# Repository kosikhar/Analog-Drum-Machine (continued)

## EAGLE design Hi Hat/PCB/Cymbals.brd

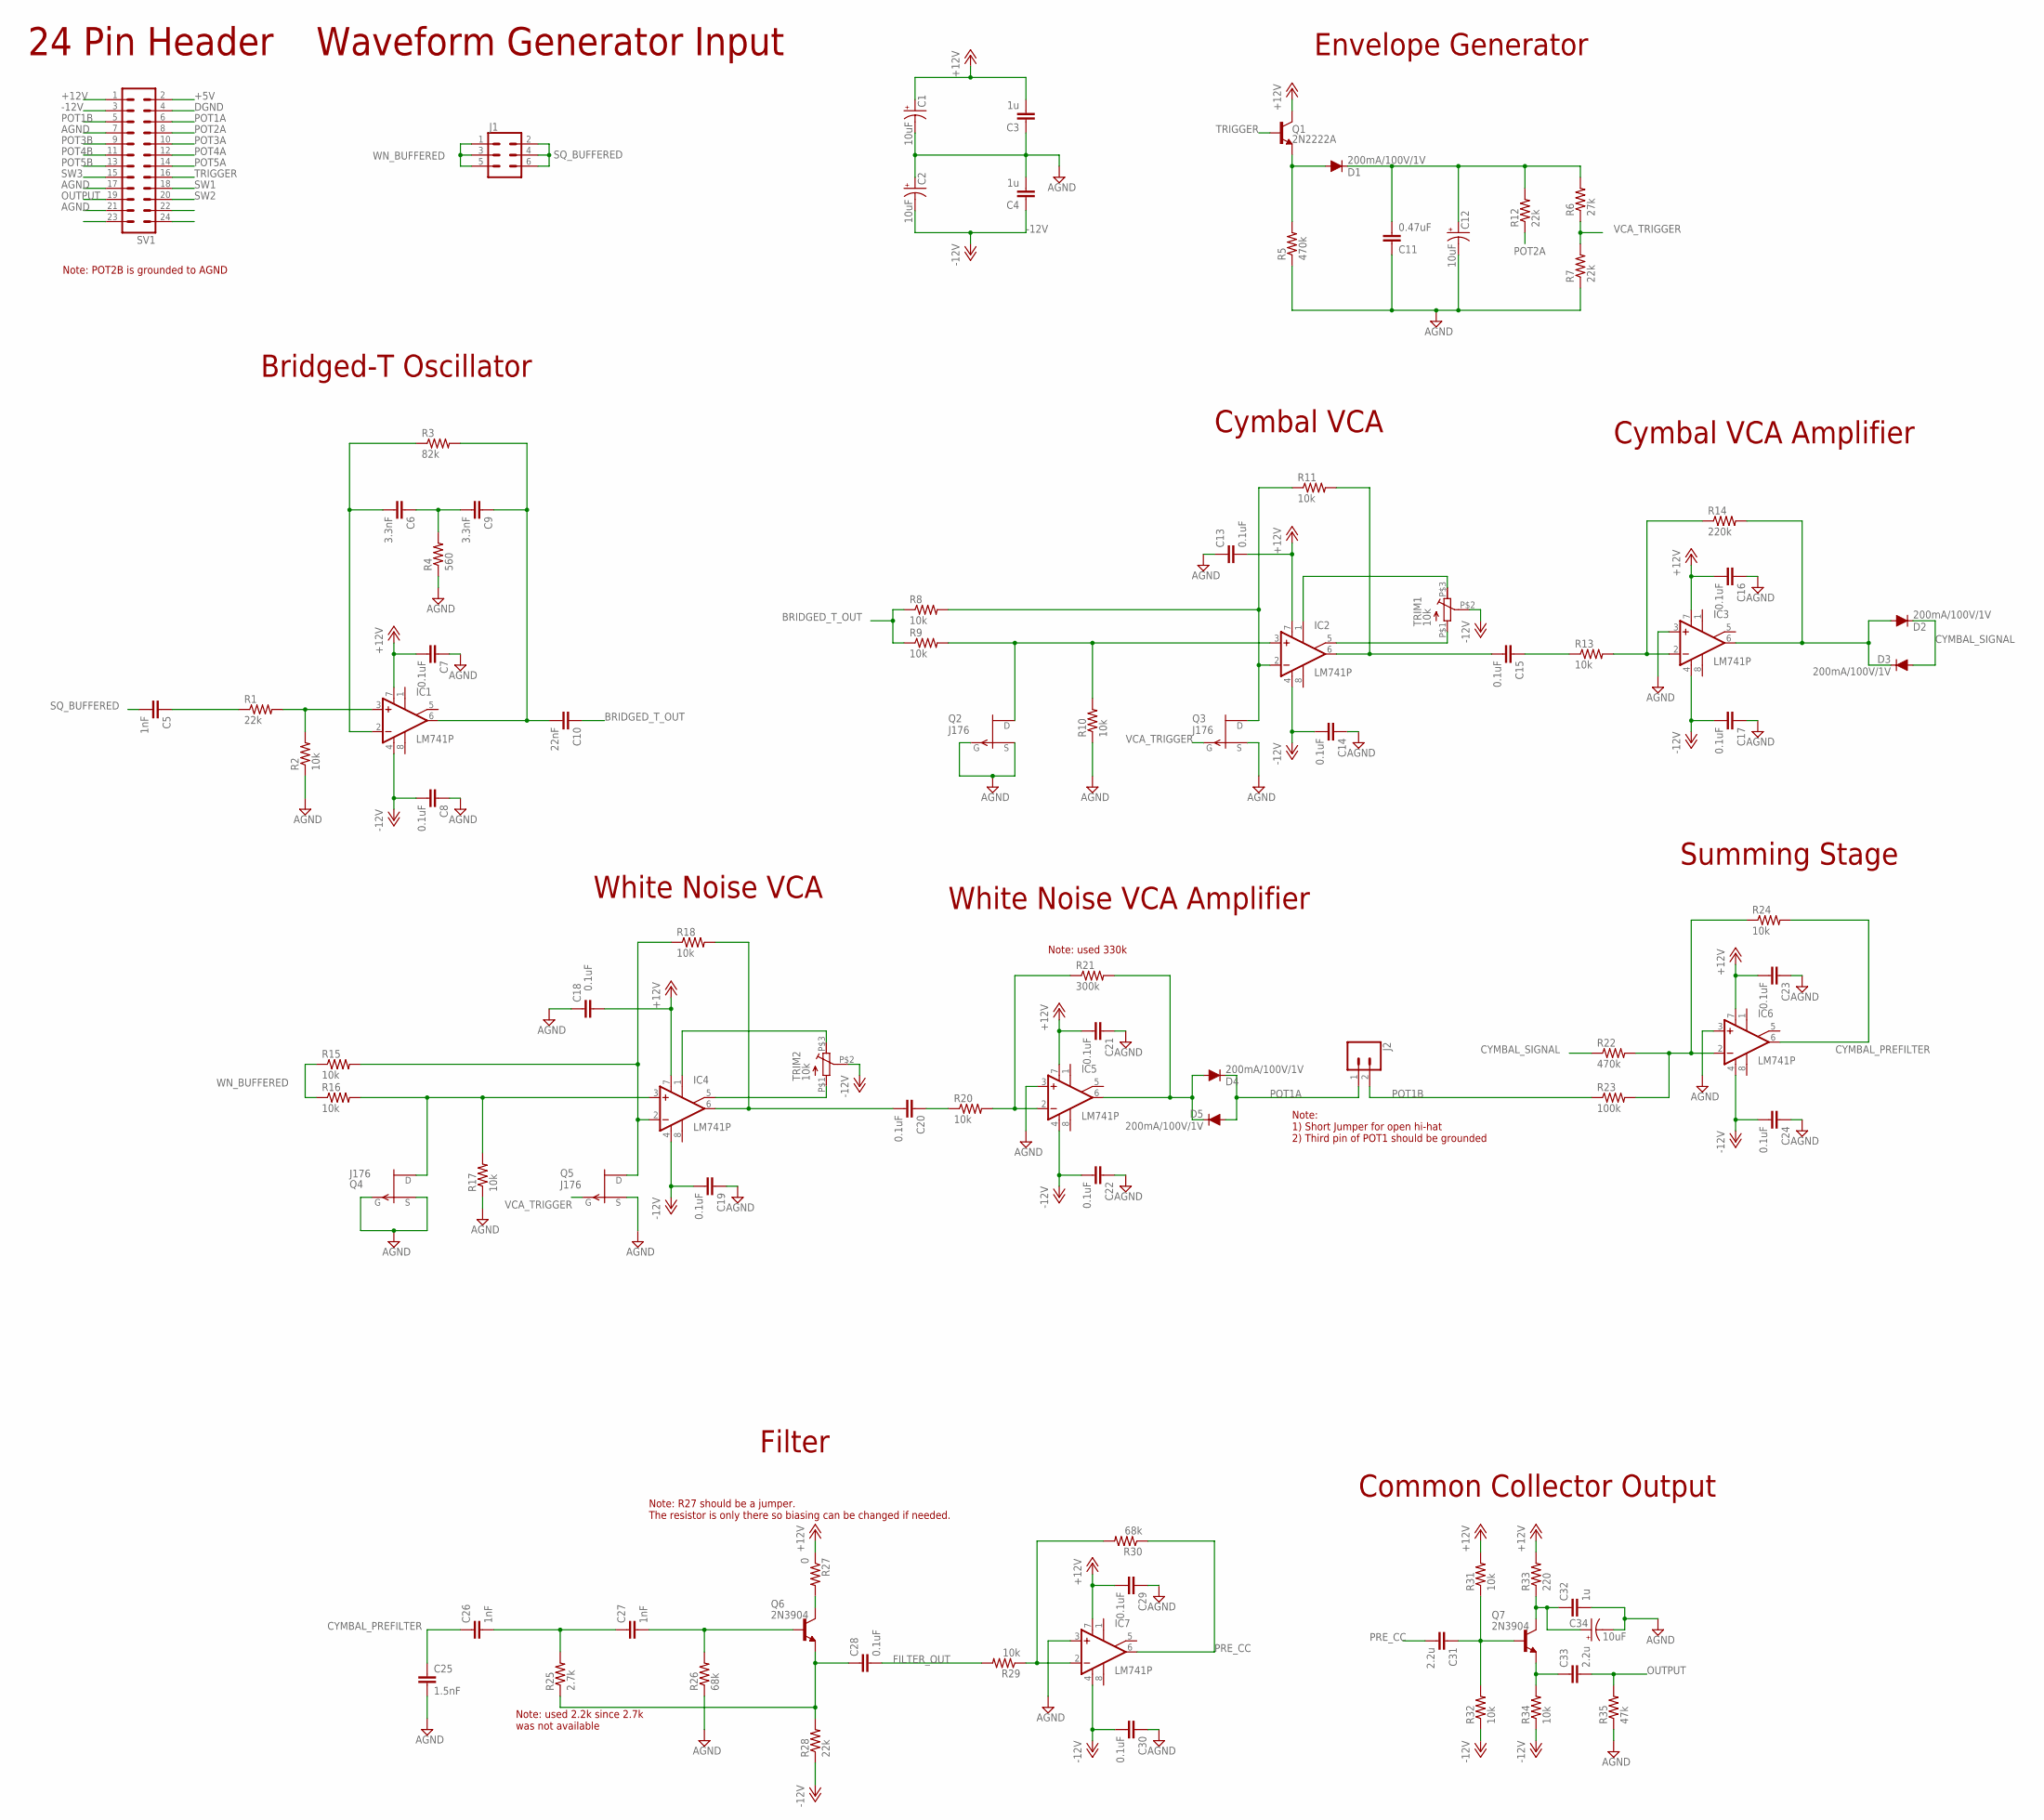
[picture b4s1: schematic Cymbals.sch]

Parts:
C1, C2, C12, C34: 10uF; E2,5-6
C3, C4, C32: 1u; C050-024X044
C5, C26, C27: 1nF; C050-024X044
C6, C9: 3.3nF; C050-024X044
C7, C8, C13, C14, C15, C16, C17, C18, C19, C20, C21, C22, C23, C24, C28, C29, C30: 0.1uF; C050-024X044
C10: 22nF; C050-024X044
C11: 0.47uF; C050-024X044
C25: 1.5nF; C050-024X044
C31, C33: 2.2u; C050-024X044
D1, D2, D3, D4, D5: 200mA/100V/1V; DIODE-1N4148
IC1, IC2, IC3, IC4, IC5, IC6, IC7: LM741P; DIL08
J1: CONN_03X2NO_SILK; 2X3-NS
J2: CONN_02; 1X02
Q1: 2N2222A; TO-92
Q2, Q3, Q4, Q5: J176; TO-92
Q6, Q7: 2N3904; TO92
R1, R7, R12, R28: 22k; 0207/7
R2, R8, R9, R10, R11, R13, R15, R16, R17, R18, R20, R24, R29, R31, R32, R34: 10k; 0207/7
R3: 82k; 0207/7
R4: 560; 0207/7
R5, R22: 470k; 0207/7
R6: 27k; 0207/7
R14: 220k; 0207/7
R21: 300k; 0207/7
R23: 100k; 0207/7
R25: 2.7k; 0207/7
R26, R30: 68k; 0207/7
R27: 0; 0207/7
R33: 220; 0207/7
R35: 47k; 0207/7
SV1: MA12-2
TRIM1, TRIM2: 10k; 10K_TRIM

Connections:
+5V: SV1.2
+12V: C1.+, C3.2, C7.2, C13.2, C16.2, C18.2, C21.2, C23.2, C29.2, IC1.7 (V+), IC2.7 (V+), IC3.7 (V+), IC4.7 (V+), IC5.7 (V+), IC6.7 (V+), IC7.7 (V+), Q1.1 (C), R27.1, R31.2, R33.2, SV1.1
-12V: C2.-, C4.1, C8.2, C14.2, C17.2, C19.2, C22.2, C24.2, C30.2, IC1.4 (V-), IC2.4 (V-), IC3.4 (V-), IC4.4 (V-), IC5.4 (V-), IC6.4 (V-), IC7.4 (V-), R28.1, R32.1, R34.1, SV1.3, TRIM1.P$2 (S), TRIM2.P$2 (S)
AGND: C1.-, C2.+, C3.1, C4.2, C7.1, C8.1, C11.1, C12.-, C13.1, C14.1, C16.1, C17.1, C18.1, C19.1, C21.1, C22.1, C23.1, C24.1, C25.2, C29.1, C30.1, C32.2, C34.-, IC3.3 (+IN), IC5.3 (+IN), IC6.3 (+IN), IC7.3 (+IN), Q2.2 (G), Q2.3 (S), Q3.3 (S), Q4.2 (G), Q4.3 (S), Q5.3 (S), R2.1, R4.1, R5.1, R7.1, R10.1, R17.1, R26.1, R35.1, SV1.7, SV1.17, SV1.21
BRIDGED_T_OUT: C10.1, R8.1, R9.1
CYMBAL_PREFILTER: C25.1, C26.1, IC6.6 (OUT), R24.2
CYMBAL_SIGNAL: D2.C, D3.A, R22.1
DGND: SV1.4
FILTER_OUT: C28.2, R29.2
unnamed: C15.2, IC2.6 (OUT), R11.2
unnamed: IC2.3 (+IN), Q2.1 (D), R9.2, R10.2
unnamed: IC2.2 (-IN), Q3.1 (D), R8.2, R11.1
unnamed: IC2.5 (ON2), TRIM1.P$1 (A)
unnamed: Q6.1 (C), R27.2
unnamed: C11.2, C12.+, D1.C, R6.2, R12.2
unnamed: IC2.1 (ON1), TRIM1.P$3 (E)
unnamed: IC3.2 (-IN), R13.2, R14.1
unnamed: IC6.2 (-IN), R22.2, R23.2, R24.1
unnamed: C6.2, IC1.2 (-IN), R3.1
unnamed: C15.1, R13.1
unnamed: IC5.2 (-IN), R20.2, R21.1
unnamed: IC7.2 (-IN), R29.1, R30.2
unnamed: C20.1, R20.1
unnamed: C20.2, IC4.6 (OUT), R18.2
unnamed: D4.A, D5.C, IC5.6 (OUT), R21.2
unnamed: D2.A, D3.C, IC3.6 (OUT), R14.2
unnamed: C6.1, C9.2, R4.2
unnamed: C9.1, C10.2, IC1.6 (OUT), R3.2
unnamed: IC1.3 (+IN), R1.2, R2.2
unnamed: C5.1, R1.1
unnamed: C31.1, Q7.2 (B), R31.1, R32.2
unnamed: D1.A, Q1.3 (E), R5.2
unnamed: IC4.3 (+IN), Q4.1 (D), R16.2, R17.2
unnamed: IC4.2 (-IN), Q5.1 (D), R15.2, R18.1
unnamed: IC4.5 (ON2), TRIM2.P$1 (A)
unnamed: IC4.1 (ON1), TRIM2.P$3 (E)
unnamed: C33.1, Q7.3 (E), R34.2
unnamed: C32.1, C34.+, Q7.1 (C), R33.1
unnamed: C26.2, C27.1, R25.2
unnamed: C27.2, Q6.2 (B), R26.2
unnamed: C28.1, Q6.3 (E), R25.1, R28.2
OUTPUT: C33.2, R35.2, SV1.19
POT1A: D4.C, D5.A, J2.1, SV1.6
POT1B: J2.2, R23.1, SV1.5
POT2A: R12.1, SV1.8
POT3A: SV1.10
POT3B: SV1.9
POT4A: SV1.12
POT4B: SV1.11
POT5A: SV1.14
POT5B: SV1.13
PRE_CC: C31.2, IC7.6 (OUT), R30.1
SQ_BUFFERED: C5.2, J1.2, J1.4, J1.6
SW1: SV1.18
SW2: SV1.20
SW3: SV1.15
TRIGGER: Q1.2 (B), SV1.16
VCA_TRIGGER: Q3.2 (G), Q5.2 (G), R6.1, R7.2
WN_BUFFERED: J1.1, J1.3, J1.5, R15.1, R16.1

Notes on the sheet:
Note: 1) Short Jumper for open hi-hat 2) Third pin of POT1 should be grounded
Note: POT2B is grounded to AGND
Note: R27 should be a jumper. The resistor is only there so biasing can be changed if needed.
Note: used 330k
Note: used 2.2k since 2.7k was not available
24 Pin Header
Waveform Generator Input
Bridged-T Oscillator
Envelope Generator
Cymbal VCA
Cymbal VCA Amplifier
White Noise VCA
White Noise VCA Amplifier
Summing Stage
Filter
Common Collector Output

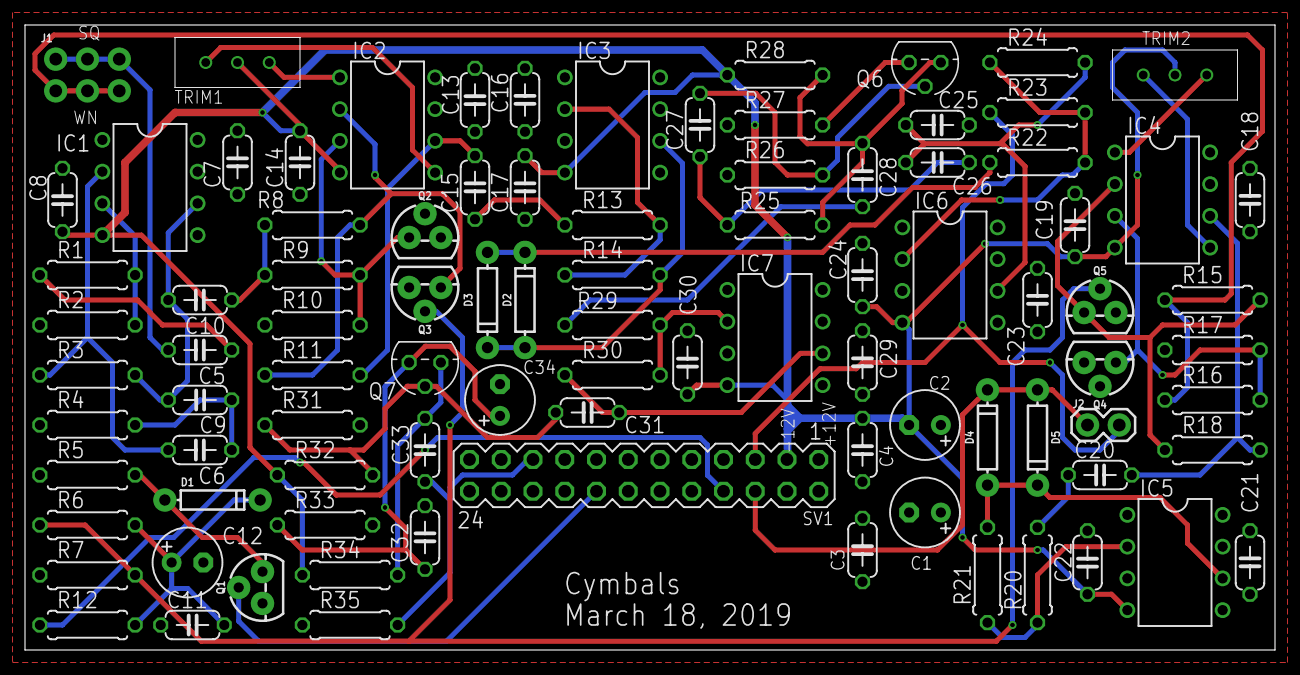
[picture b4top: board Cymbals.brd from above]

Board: 2 copper layers, 100.0 x 50.0 mm, 92 parts (0 on the bottom side), 48 nets.

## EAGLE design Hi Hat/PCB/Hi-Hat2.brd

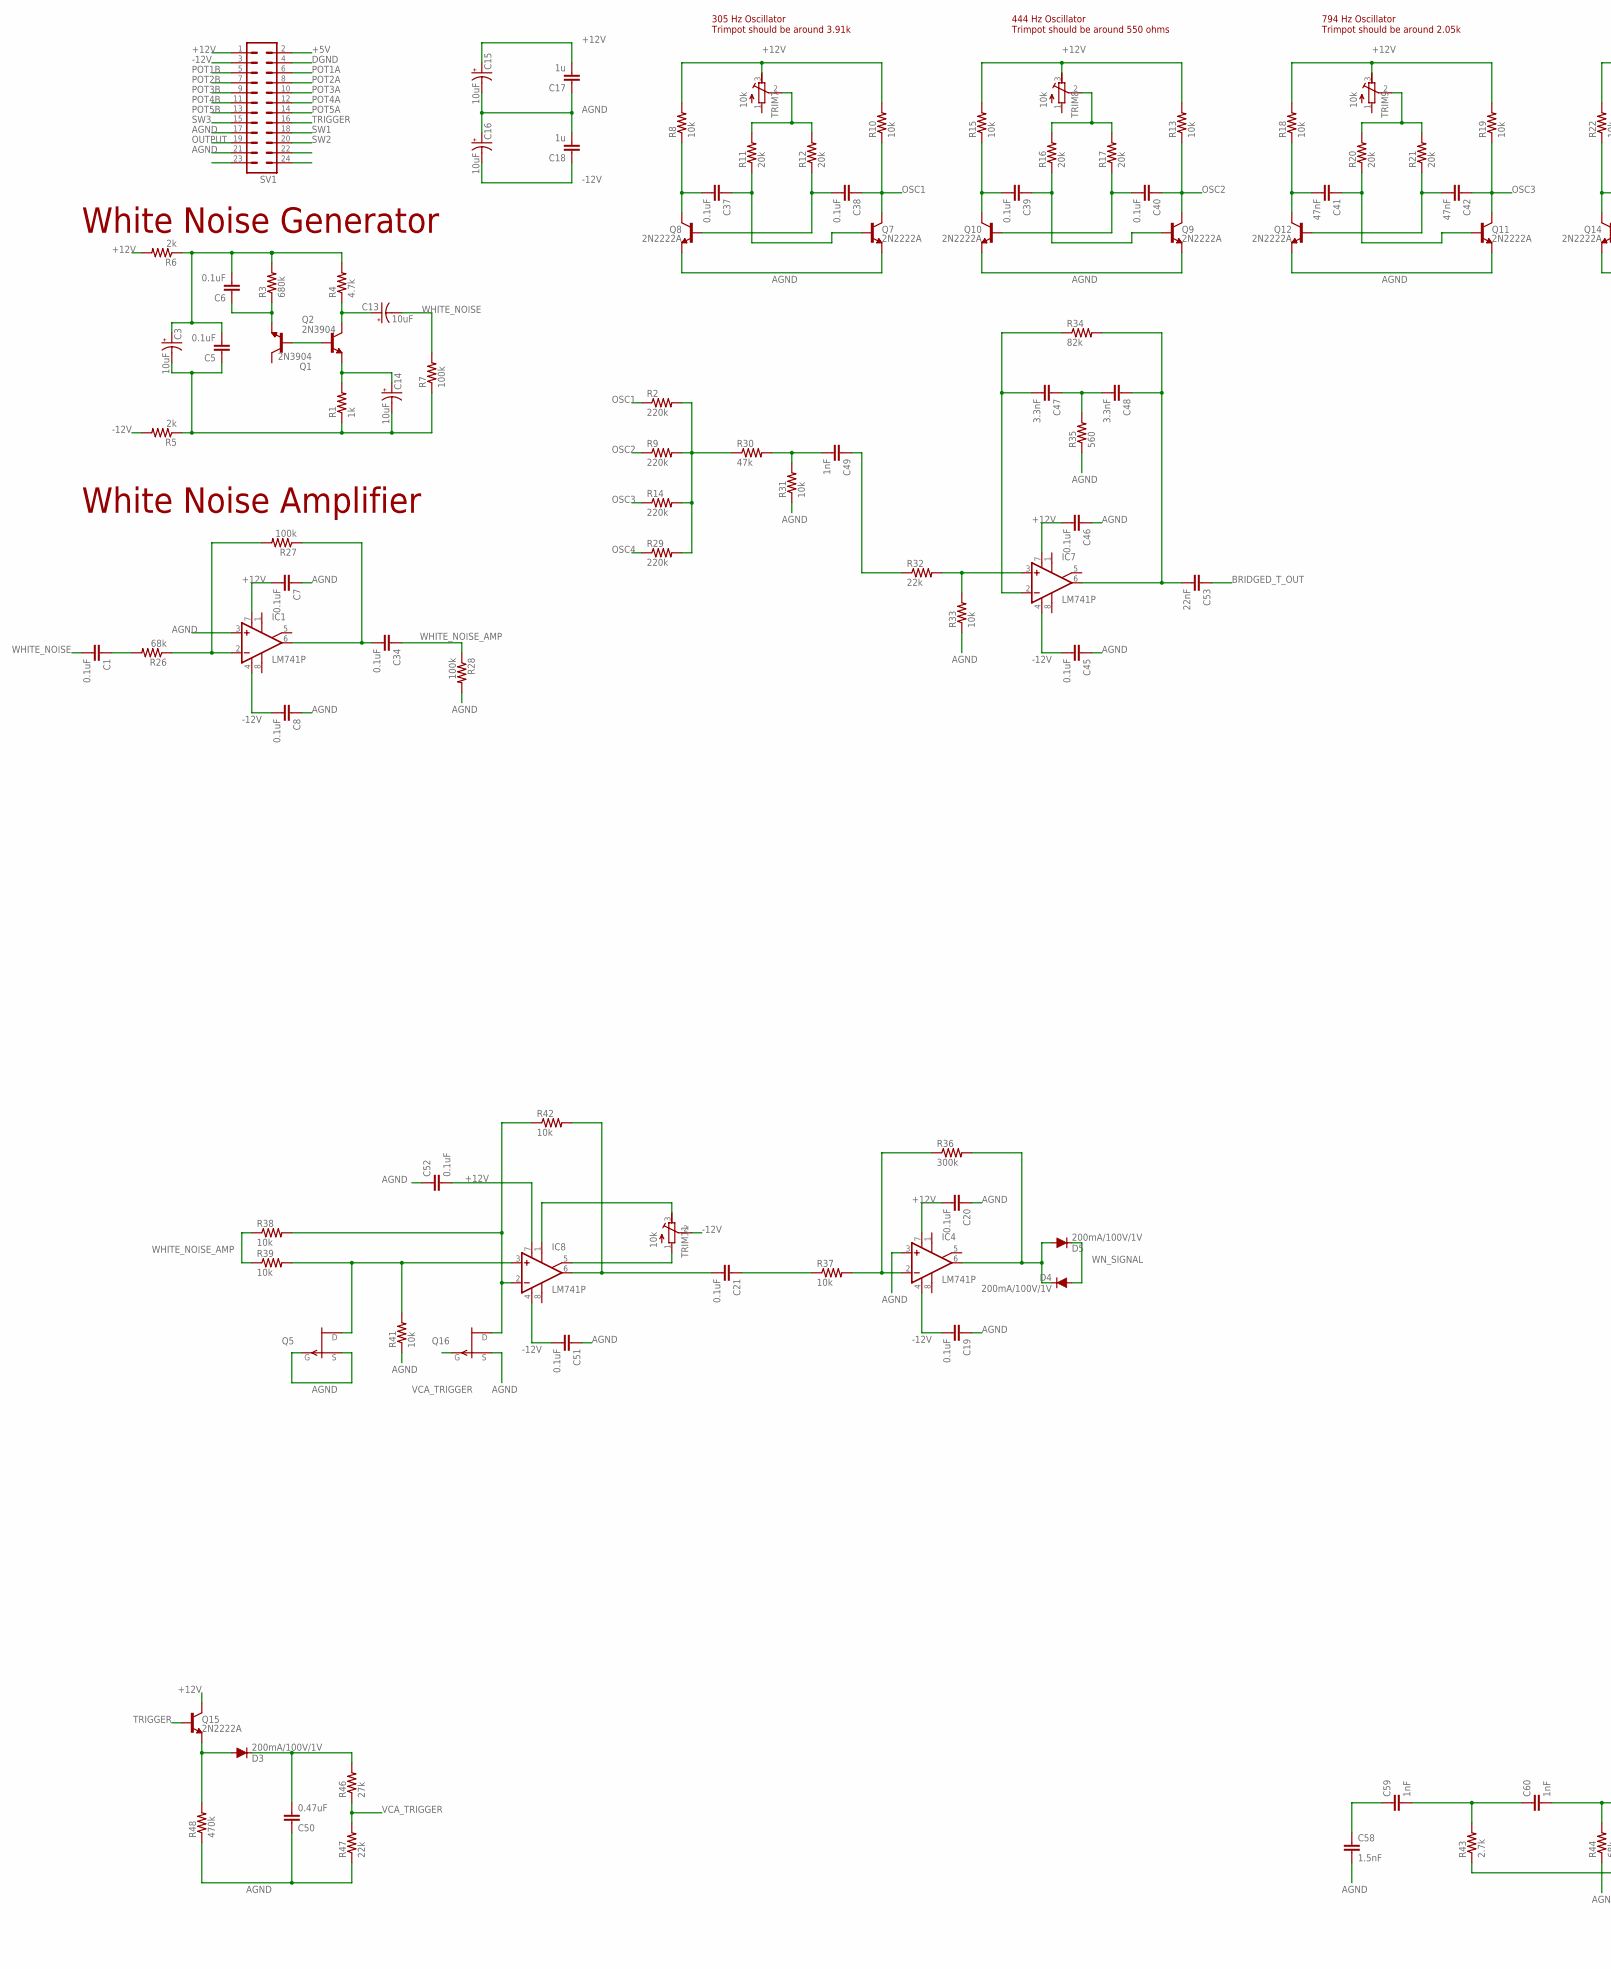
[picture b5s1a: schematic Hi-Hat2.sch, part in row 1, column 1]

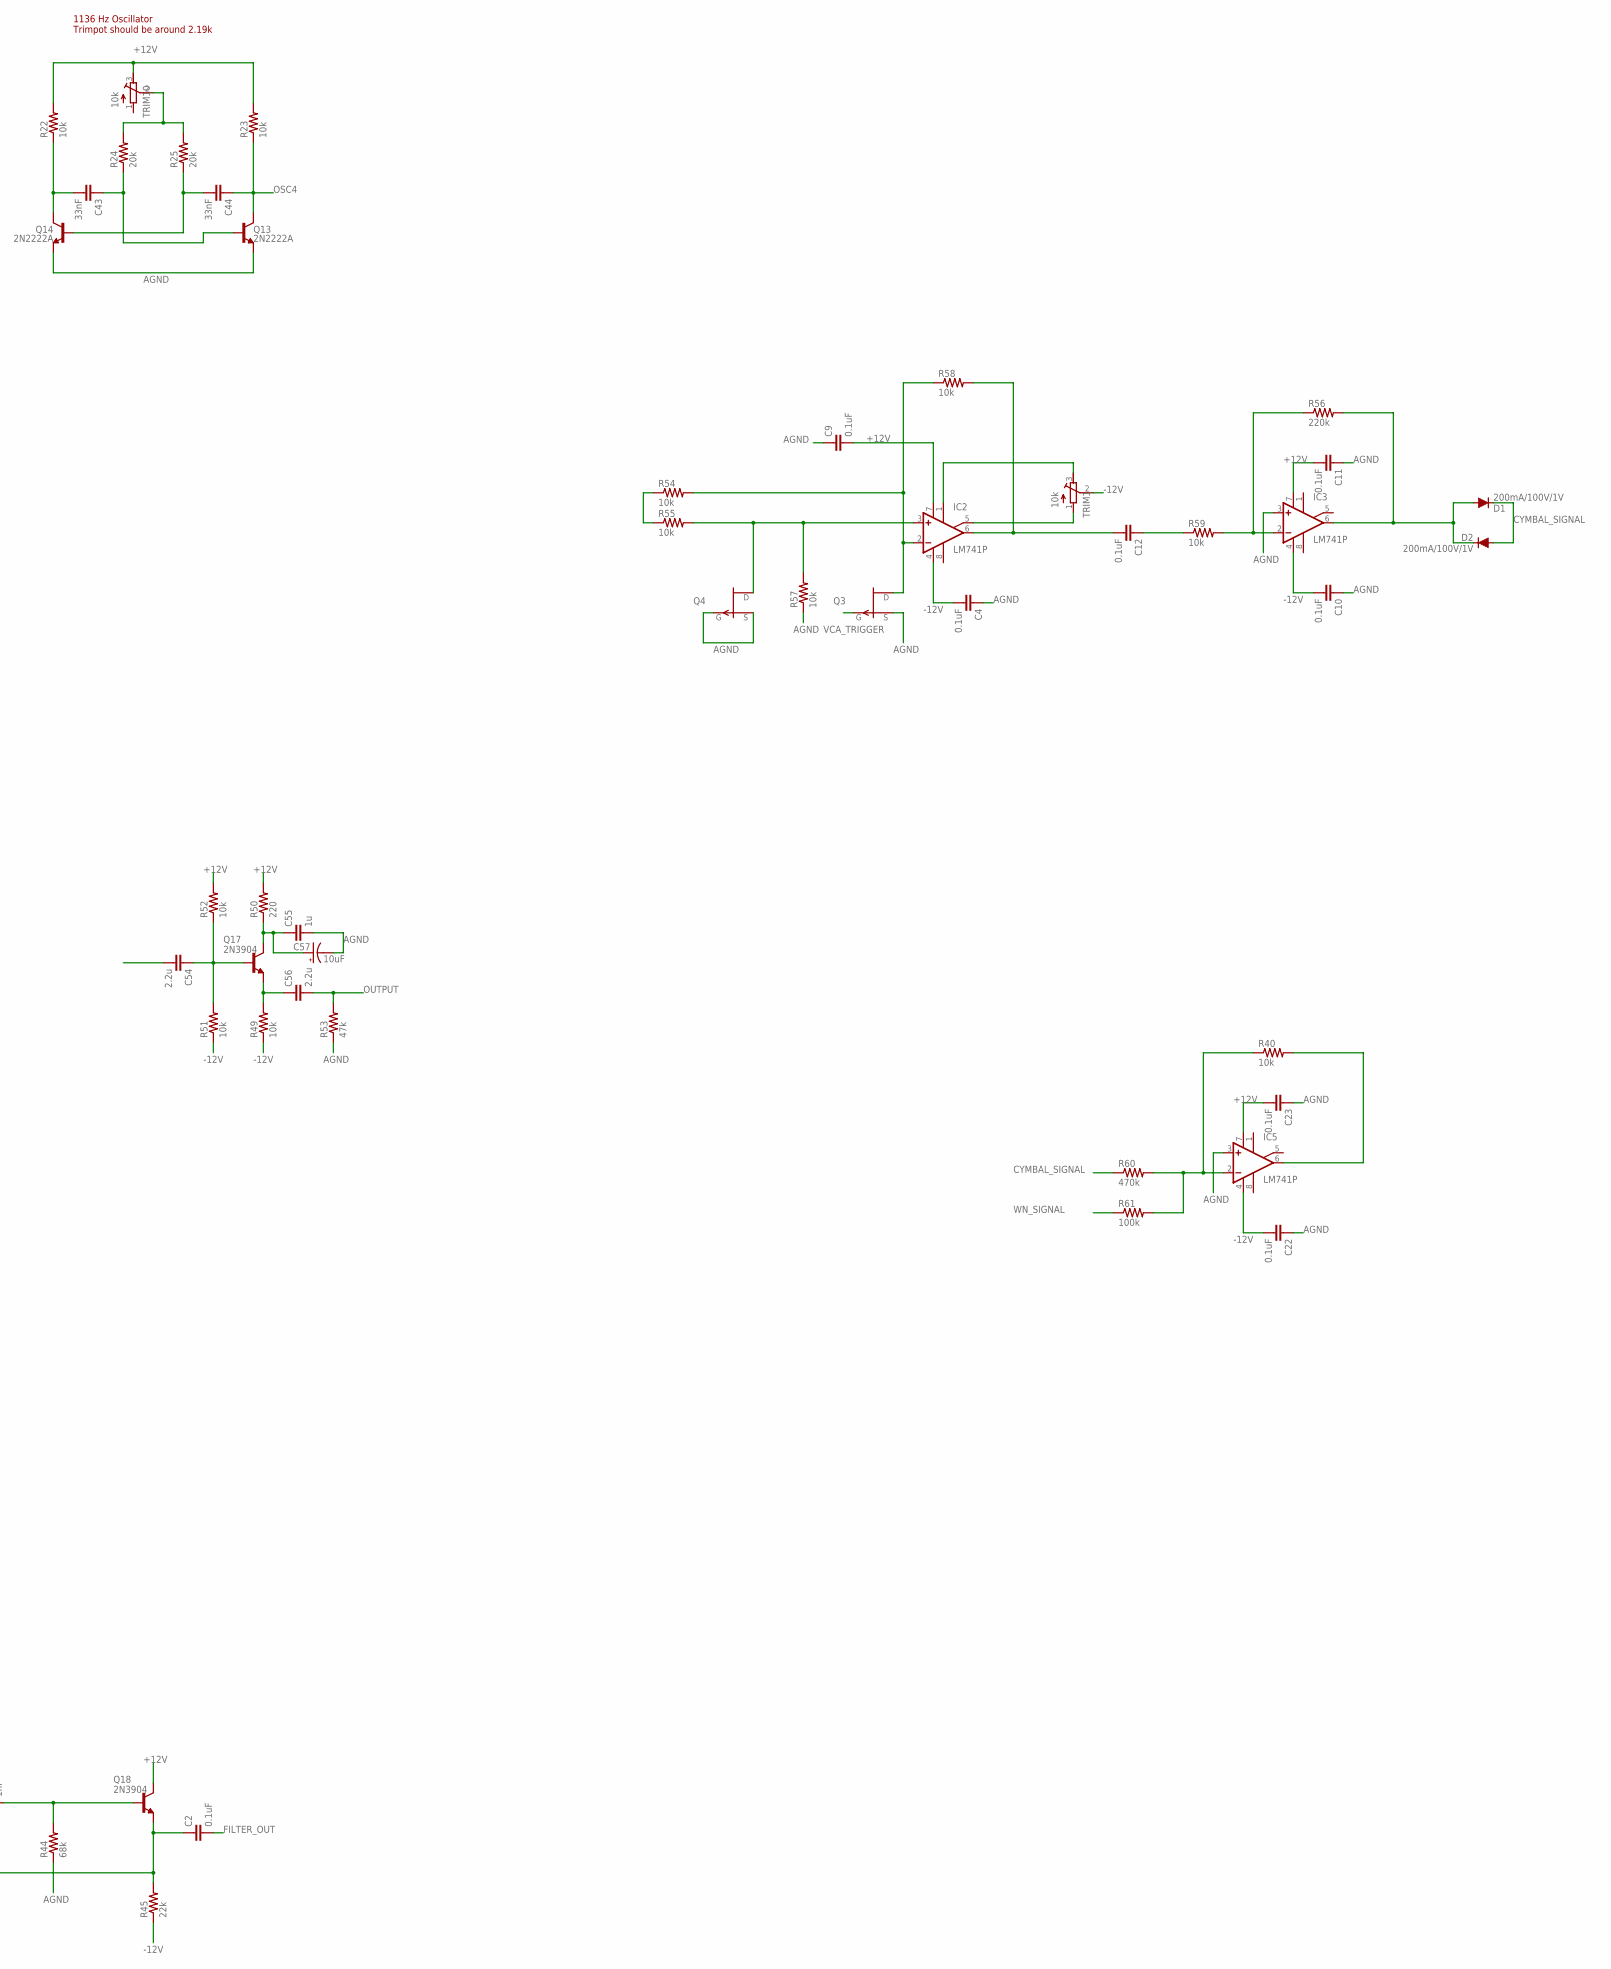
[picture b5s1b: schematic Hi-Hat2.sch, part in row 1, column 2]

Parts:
C1, C2, C4, C5, C6, C7, C8, C9, C10, C11, C12, C19, C20, C21, C22, C23, C34, C37, C38, C39, C40, C45, C46, C51, C52: 0.1uF; C050-024X044
C3, C13, C14, C15, C16, C57: 10uF; E2,5-6
C17, C18, C55: 1u; C050-024X044
C41, C42: 47nF; C050-024X044
C43, C44: 33nF; C050-024X044
C47, C48: 3.3nF; C050-024X044
C49, C59, C60: 1nF; C050-024X044
C50: 0.47uF; C050-024X044
C53: 22nF; C050-024X044
C54, C56: 2.2u; C050-024X044
C58: 1.5nF; C050-024X044
D1, D2, D3, D4, D5: 200mA/100V/1V; DIODE-1N4148
IC1, IC2, IC3, IC4, IC5, IC7, IC8: LM741P; DIL08
Q1, Q2, Q17, Q18: 2N3904; TO92
Q3, Q4, Q5, Q16: J176; TO-92
Q7, Q8, Q9, Q10, Q11, Q12, Q13, Q14, Q15: 2N2222A; TO-92
R1: 1k; 0207/7
R2, R9, R14, R29, R56: 220k; 0207/7
R3: 680k; 0207/7
R4: 4.7k; 0207/7
R5, R6: 2k; 0207/7
R7, R27, R28, R61: 100k; 0207/7
R8, R10, R13, R15, R18, R19, R22, R23, R31, R33, R37, R38, R39, R40, R41, R42, R49, R51, R52, R54, R55, R57, R58, R59: 10k; 0207/7
R11, R12, R16, R17, R20, R21, R24, R25: 20k; 0207/7
R26, R44: 68k; 0207/7
R30, R53: 47k; 0207/7
R32, R45, R47: 22k; 0207/7
R34: 82k; 0207/7
R35: 560; 0207/7
R36: 300k; 0207/7
R43: 2.7k; 0207/7
R46: 27k; 0207/7
R48, R60: 470k; 0207/7
R50: 220; 0207/7
SV1: MA12-2
TRIM1, TRIM7, TRIM8, TRIM9, TRIM10, TRIM11: 10k; RTRIM64W

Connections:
+5V: SV1.2
+12V: C7.2, C9.2, C11.2, C15.+, C17.2, C20.2, C23.2, C46.2, C52.2, IC1.7 (V+), IC2.7 (V+), IC3.7 (V+), IC4.7 (V+), IC5.7 (V+), IC7.7 (V+), IC8.7 (V+), Q15.1 (C), Q18.1 (C), R6.2, R8.2, R10.2, R13.2, R15.2, R18.2, R19.2, R22.2, R23.2, R50.2, R52.2, SV1.1, TRIM7.3 (E), TRIM8.3 (E), TRIM9.3 (E), TRIM10.3 (E)
-12V: C4.2, C8.2, C10.2, C16.-, C18.1, C19.2, C22.2, C45.2, C51.2, IC1.4 (V-), IC2.4 (V-), IC3.4 (V-), IC4.4 (V-), IC5.4 (V-), IC7.4 (V-), IC8.4 (V-), R5.2, R45.1, R49.1, R51.1, SV1.3, TRIM1.2 (S), TRIM11.2 (S)
AGND: C4.1, C7.1, C8.1, C9.1, C10.1, C11.1, C15.-, C16.+, C17.1, C18.2, C19.1, C20.1, C22.1, C23.1, C45.1, C46.1, C50.1, C51.1, C52.1, C55.2, C57.-, C58.2, IC1.3 (+IN), IC3.3 (+IN), IC4.3 (+IN), IC5.3 (+IN), Q3.3 (S), Q4.2 (G), Q4.3 (S), Q5.2 (G), Q5.3 (S), Q7.3 (E), Q8.3 (E), Q9.3 (E), Q10.3 (E), Q11.3 (E), Q12.3 (E), Q13.3 (E), Q14.3 (E), Q16.3 (S), R28.2, R31.1, R33.1, R35.1, R41.1, R44.1, R47.1, R48.1, R53.1, R57.1, SV1.17, SV1.21
BRIDGED_T_OUT: C53.1
CC_INPUT1: C54.2
CYMBAL_SIGNAL: D1.C, D2.A, R60.1
DGND: SV1.4
FILTER_OUT: C2.2
unnamed: C50.2, D3.C, R46.2
unnamed: IC2.3 (+IN), Q4.1 (D), R55.2, R57.2
unnamed: IC2.2 (-IN), Q3.1 (D), R54.2, R58.1
unnamed: IC2.5 (ON2), TRIM1.1 (A)
unnamed: C14.+, Q2.3 (E), R1.2
unnamed: C3.+, C5.2, C6.2, R3.2, R4.2, R6.1
unnamed: IC2.1 (ON1), TRIM1.3 (E)
unnamed: IC3.2 (-IN), R56.1, R59.2
unnamed: C34.2, IC1.6 (OUT), R27.1
unnamed: IC5.2 (-IN), R40.1, R60.2, R61.2
unnamed: C37.2, Q8.1 (C), R8.1
unnamed: C37.1, Q7.2 (B), R11.1
unnamed: C38.2, Q8.2 (B), R12.1
unnamed: C47.2, IC7.2 (-IN), R34.1
unnamed: R11.2, R12.2, TRIM7.2 (S)
unnamed: C39.2, Q10.1 (C), R15.1
unnamed: Q1.2 (B), Q2.2 (B)
unnamed: C39.1, Q9.2 (B), R16.1
unnamed: C40.2, Q10.2 (B), R17.1
unnamed: C6.1, Q1.3 (E), R3.1
unnamed: C3.-, C5.1, C14.-, R1.1, R5.1, R7.1
unnamed: R2.2, R9.2, R14.2, R29.2, R30.1
unnamed: IC1.2 (-IN), R26.1, R27.2
unnamed: C12.1, R59.1
unnamed: C1.1, R26.2
unnamed: R16.2, R17.2, TRIM8.2 (S)
unnamed: C13.+, Q2.1 (C), R4.1
unnamed: C41.2, Q12.1 (C), R18.1
unnamed: IC4.2 (-IN), R36.1, R37.2
unnamed: C21.1, R37.1
unnamed: C41.1, Q11.2 (B), R20.1
unnamed: C21.2, IC8.6 (OUT), R42.2
unnamed: IC5.6 (OUT), R40.2
unnamed: D4.C, D5.A, IC4.6 (OUT), R36.2
unnamed: D1.A, D2.C, IC3.6 (OUT), R56.2
unnamed: C42.2, Q12.2 (B), R21.1
unnamed: C47.1, C48.2, R35.2
unnamed: R20.2, R21.2, TRIM9.2 (S)
unnamed: C43.2, Q14.1 (C), R22.1
unnamed: C43.1, Q13.2 (B), R24.1
unnamed: C44.2, Q14.2 (B), R25.1
unnamed: C49.2, R30.2, R31.2
unnamed: R24.2, R25.2, TRIM10.2 (S)
unnamed: C48.1, C53.2, IC7.6 (OUT), R34.2
unnamed: IC7.3 (+IN), R32.2, R33.2
unnamed: C49.1, R32.1
unnamed: C54.1, Q17.2 (B), R51.2, R52.1
unnamed: D3.A, Q15.3 (E), R48.2
unnamed: IC8.3 (+IN), Q5.1 (D), R39.2, R41.2
unnamed: IC8.2 (-IN), Q16.1 (D), R38.2, R42.1
unnamed: IC8.5 (ON2), TRIM11.1 (A)
unnamed: IC8.1 (ON1), TRIM11.3 (E)
unnamed: C56.1, Q17.3 (E), R49.2
unnamed: C55.1, C57.+, Q17.1 (C), R50.1
unnamed: C59.2, C60.1, R43.2
unnamed: C60.2, Q18.2 (B), R44.2
unnamed: C2.1, Q18.3 (E), R43.1, R45.2
OSC1: C38.1, Q7.1 (C), R2.1, R10.1
OSC2: C40.1, Q9.1 (C), R9.1, R13.1
OSC3: C42.1, Q11.1 (C), R14.1, R19.1
OSC4: C44.1, Q13.1 (C), R23.1, R29.1
OUTPUT: C56.2, R53.2, SV1.19
POT1A: SV1.6
POT1B: SV1.5
POT2A: SV1.8
POT2B: SV1.7
POT3A: SV1.10
POT3B: SV1.9
POT4A: SV1.12
POT4B: SV1.11
POT5A: SV1.14
POT5B: SV1.13
SW1: C58.1, C59.1, SV1.18
SW2: SV1.20
SW3: SV1.15
SW4: C12.2, IC2.6 (OUT), R58.2
TRIGGER: Q15.2 (B), SV1.16
VCA_INPUT1: R54.1, R55.1
VCA_TRIGGER: Q3.2 (G), Q16.2 (G), R46.1, R47.2
WHITE_NOISE: C1.2, C13.-, R7.2
WHITE_NOISE_AMP: C34.1, R28.1, R38.1, R39.1
WN_SIGNAL: D4.A, D5.C, R61.1

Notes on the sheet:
White Noise Generator
White Noise Amplifier
305 Hz Oscillator Trimpot should be around 3.91k
444 Hz Oscillator Trimpot should be around 550 ohms
794 Hz Oscillator Trimpot should be around 2.05k
1136 Hz Oscillator Trimpot should be around 2.19k

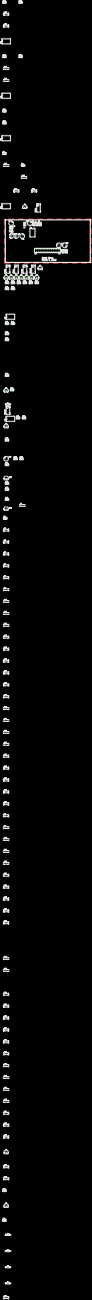
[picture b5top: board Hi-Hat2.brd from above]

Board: 2 copper layers, 100.0 x 50.0 mm, 145 parts (0 on the bottom side), 74 nets.

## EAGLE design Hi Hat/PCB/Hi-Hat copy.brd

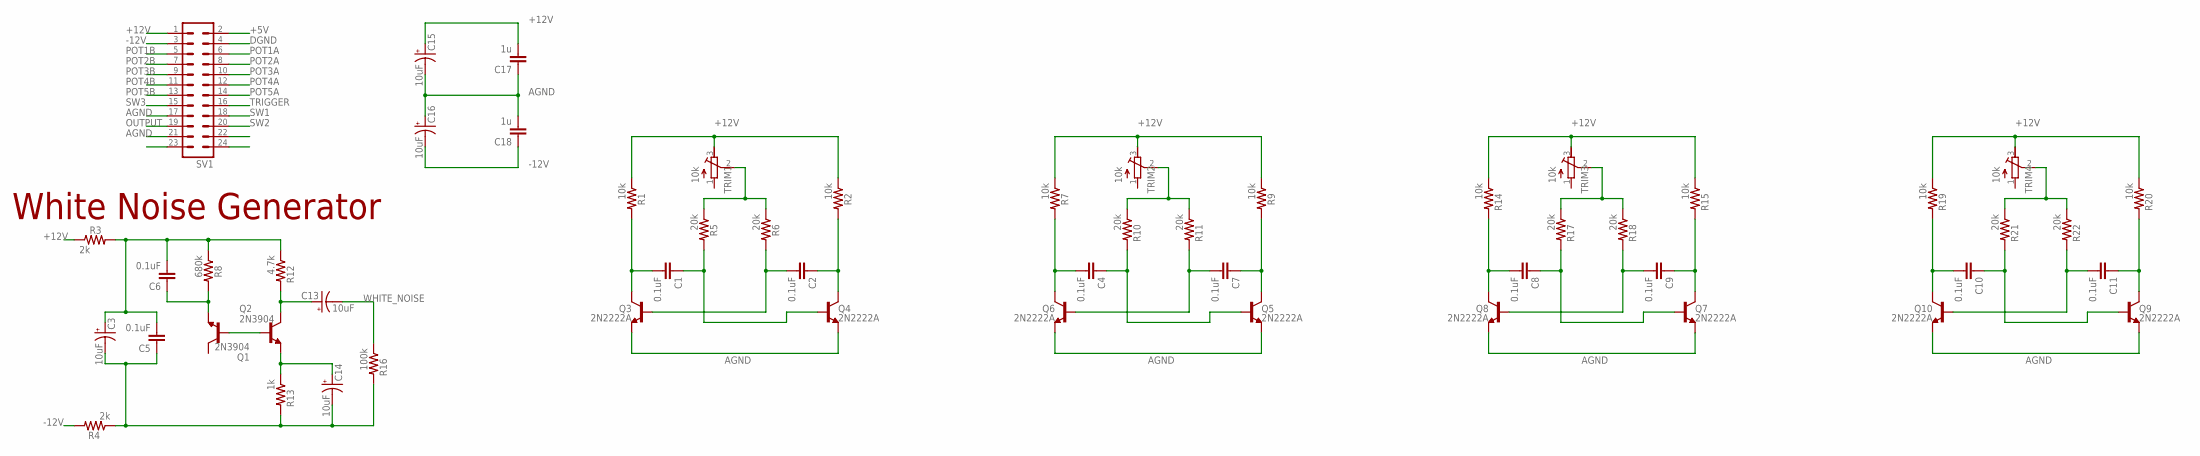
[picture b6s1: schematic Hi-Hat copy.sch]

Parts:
C1, C2, C4, C5, C6, C7, C8, C9, C10, C11: 0.1uF; C050-024X044
C3, C13, C14, C15, C16: 10uF; E2,5-6
C17, C18: 1u; C050-024X044
Q1, Q2: 2N3904; TO92
Q3, Q4, Q5, Q6, Q7, Q8, Q9, Q10: 2N2222A; TO-92
R1, R2, R7, R9, R14, R15, R19, R20: 10k; 0207/10
R3, R4: 2k; 0207/10
R5, R6, R10, R11, R17, R18, R21, R22: 20k; 0207/10
R8: 680k; 0207/10
R12: 4.7k; 0207/10
R13: 1k; 0207/10
R16: 100k; 0207/10
SV1: MA12-2
TRIM1, TRIM2, TRIM3, TRIM4: 10k; RTRIM64W

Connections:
+5V: SV1.2
+12V: C15.+, C17.2, R1.1, R2.1, R3.1, R7.1, R9.1, R14.1, R15.1, R19.1, R20.1, SV1.1, TRIM1.3 (E), TRIM2.3 (E), TRIM3.3 (E), TRIM4.3 (E)
-12V: C16.-, C18.1, R4.2, SV1.3
AGND: C15.-, C16.+, C17.1, C18.2, Q3.3 (E), Q4.3 (E), Q5.3 (E), Q6.3 (E), Q7.3 (E), Q8.3 (E), Q9.3 (E), Q10.3 (E), SV1.17, SV1.21
DGND: SV1.4
unnamed: C1.2, Q3.1 (C), R1.2
unnamed: C1.1, Q4.2 (B), R5.2
unnamed: C2.2, Q3.2 (B), R6.2
unnamed: C2.1, Q4.1 (C), R2.2
unnamed: C14.+, Q2.3 (E), R13.1
unnamed: C3.+, C5.2, C6.2, R3.2, R8.1, R12.1
unnamed: C4.2, Q6.1 (C), R7.2
unnamed: R5.1, R6.1, TRIM1.2 (S)
unnamed: C4.1, Q5.2 (B), R10.2
unnamed: C7.2, Q6.2 (B), R11.2
unnamed: C7.1, Q5.1 (C), R9.2
unnamed: R10.1, R11.1, TRIM2.2 (S)
unnamed: C8.2, Q8.1 (C), R14.2
unnamed: C8.1, Q7.2 (B), R17.2
unnamed: C9.2, Q8.2 (B), R18.2
unnamed: C9.1, Q7.1 (C), R15.2
unnamed: Q1.2 (B), Q2.2 (B)
unnamed: R17.1, R18.1, TRIM3.2 (S)
unnamed: C10.2, Q10.1 (C), R19.2
unnamed: C6.1, Q1.3 (E), R8.2
unnamed: C3.-, C5.1, C14.-, R4.1, R13.2, R16.2
unnamed: C10.1, Q9.2 (B), R21.2
unnamed: C11.2, Q10.2 (B), R22.2
unnamed: C11.1, Q9.1 (C), R20.2
unnamed: R21.1, R22.1, TRIM4.2 (S)
unnamed: C13.+, Q2.1 (C), R12.2
OUTPUT: SV1.19
POT1A: SV1.6
POT1B: SV1.5
POT2A: SV1.8
POT2B: SV1.7
POT3A: SV1.10
POT3B: SV1.9
POT4A: SV1.12
POT4B: SV1.11
POT5A: SV1.14
POT5B: SV1.13
SW1: SV1.18
SW2: SV1.20
SW3: SV1.15
TRIGGER: SV1.16
WHITE_NOISE: C13.-, R16.1

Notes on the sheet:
White Noise Generator

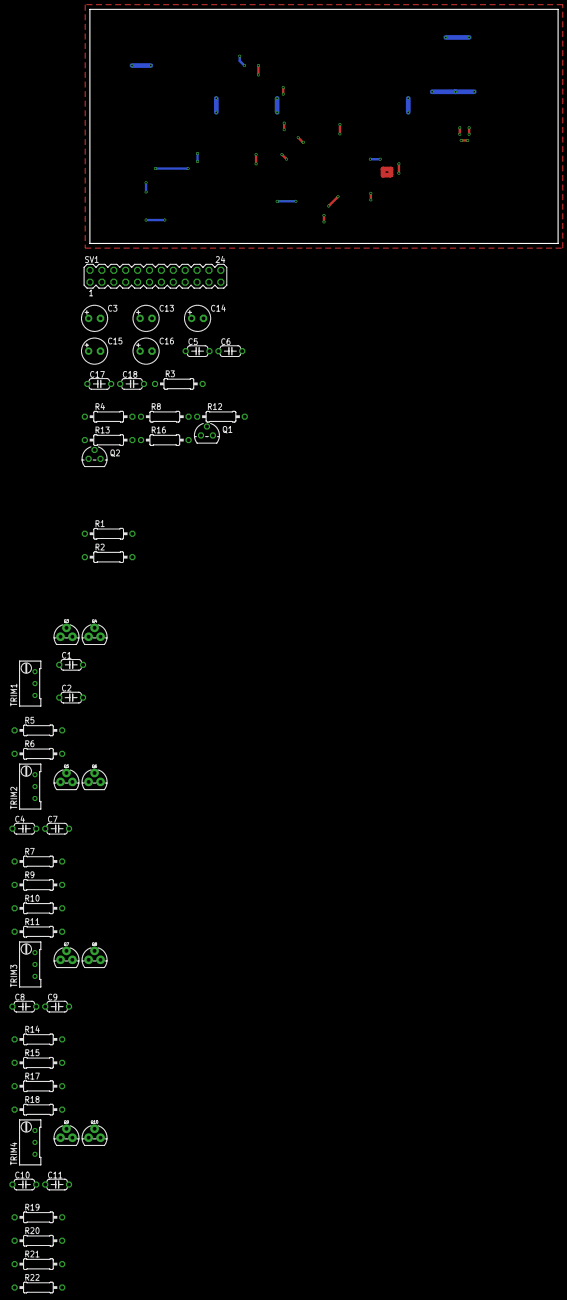
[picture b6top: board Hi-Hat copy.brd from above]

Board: 2 copper layers, 100.0 x 50.0 mm, 54 parts (0 on the bottom side), 30 nets.
